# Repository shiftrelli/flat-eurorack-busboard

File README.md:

# flat-eurorack-busboard

A flat back Eurorack Busboard

406x30mm

free to use copy change manufacture and distribute

BOM

2x 1k 0804 resistor

1x 220 0804 resistor

2x led red 0804

1x led green 0804

17 x 2x8 P 16 pin 2.54 mm SMT Pin Header (or 5 for the small version)

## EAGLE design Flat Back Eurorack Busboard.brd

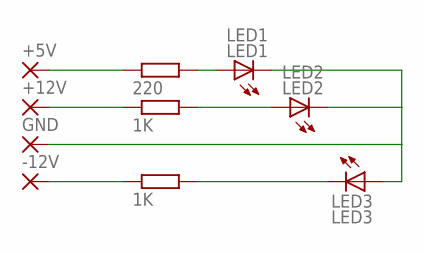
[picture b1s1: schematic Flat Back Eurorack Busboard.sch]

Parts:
+5V, +12V: SMD5; SMD2,54-5,08
-12V: SMD5; SMD2,54-5,08
GND: SMD5; SMD2,54-5,08
LED1: LED1; CHIPLED_0805
LED2: LED2; CHIPLED_0805
LED3: LED3; CHIPLED_0805
R1: 220; M0805
R2, R3: 1K; M0805

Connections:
+5V: +5V.1, R1.1
+12V: +12V.1, R2.1
-12V: -12V.1, R3.1
GND: GND.1, LED1.C, LED2.C, LED3.A
unnamed: LED1.A, R1.2
unnamed: LED2.A, R2.2
unnamed: LED3.C, R3.2

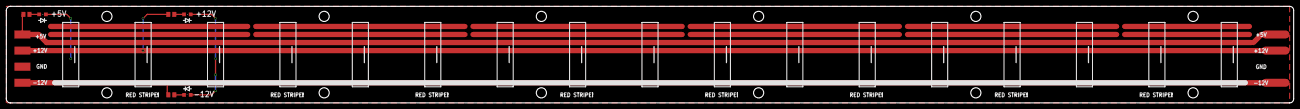
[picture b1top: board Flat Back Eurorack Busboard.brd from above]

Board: 2 copper layers, 406.4 x 30.5 mm, 10 parts (0 on the bottom side), 7 nets.
